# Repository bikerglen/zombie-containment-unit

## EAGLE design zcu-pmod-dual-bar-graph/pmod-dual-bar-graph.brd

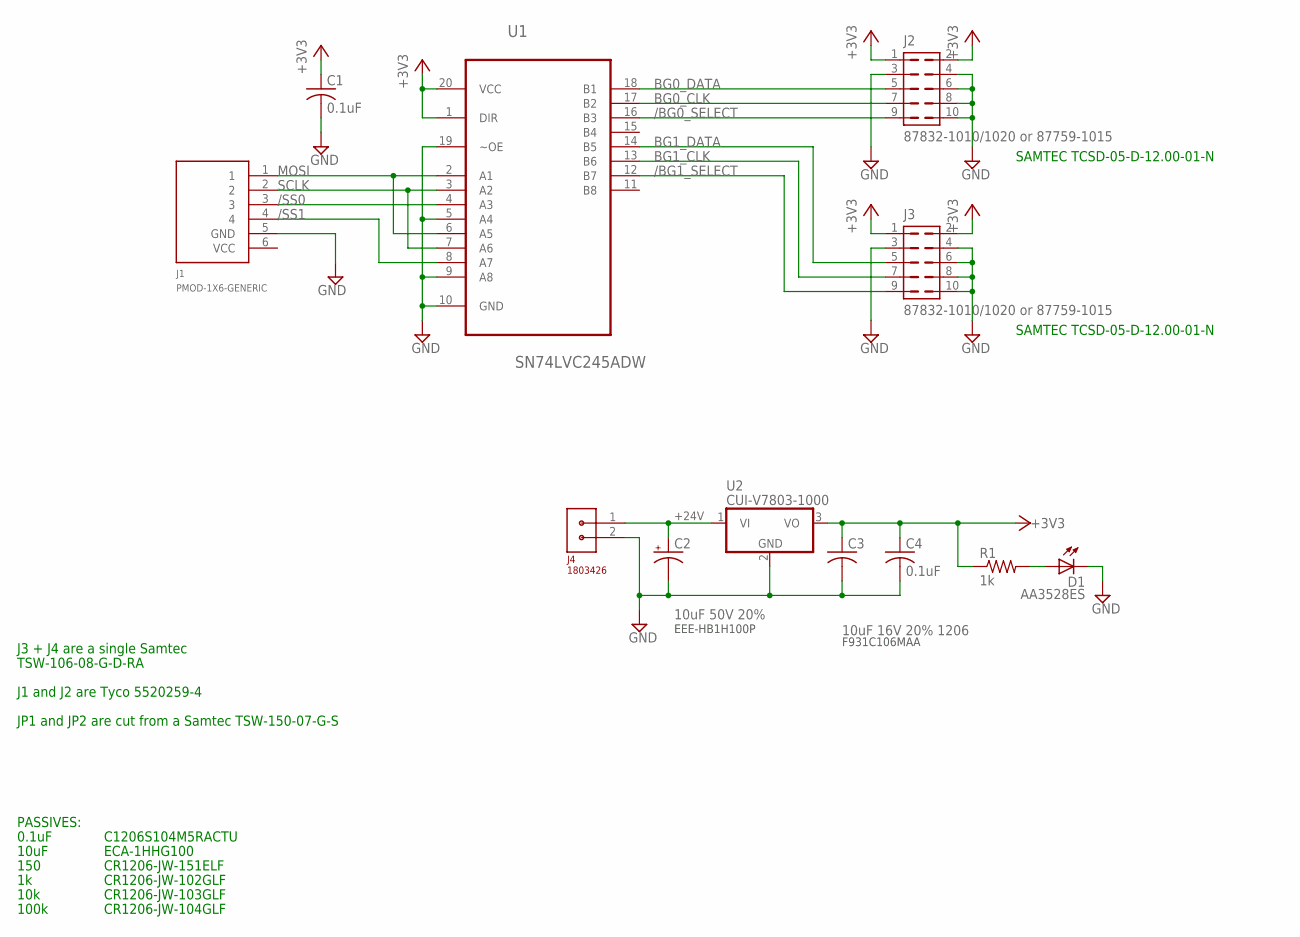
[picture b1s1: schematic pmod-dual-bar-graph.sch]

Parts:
C1, C4: 0.1uF; C1206
C2: 10uF 50V 20%; PANASONIC_D
C3: 10uF 16V 20% 1206; C1206
D1: AA3528ES; KA-3528ASYC
J1: PMOD-1X6-GENERIC; CON-PMOD-1X6
J2, J3: 87832-1010/1020 or 87759-1015; 87832-10
J4: 1803426; CON-PHOENIX-1803426-3.81-1X2
R1: 1k; R1206
U1: SN74LVC245ADW; SOIC127P1030X265-20N
U2: CUI-V7803-1000; CUI-78XX-1000

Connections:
+3V3: C1.1, C3.1, C4.1, J2.1, J2.2, J3.1, J3.2, R1.1, U1.1 (DIR), U1.20 (VCC), U2.3 (VO)
+24V: C2.+, J4.1, U2.1 (VI)
/BG0_SELECT: J2.9, U1.16 (B3)
/BG1_SELECT: J3.9, U1.12 (B7)
/SS0: J1.3, U1.4 (A3)
/SS1: J1.4, U1.8 (A7)
BG0_CLK: J2.7, U1.17 (B2)
BG0_DATA: J2.5, U1.18 (B1)
BG1_CLK: J3.7, U1.13 (B6)
BG1_DATA: J3.5, U1.14 (B5)
GND: C1.2, C2.-, C3.2, C4.2, D1.C, J1.5 (GND), J2.3, J2.4, J2.6, J2.8, J2.10, J3.3, J3.4, J3.6, J3.8, J3.10, J4.2, U1.5 (A4), U1.9 (A8), U1.10 (GND), U1.19 (~OE), U2.2 (GND)
MOSI: J1.1, U1.2 (A1), U1.6 (A5)
unnamed: D1.A, R1.2
SCLK: J1.2, U1.3 (A2), U1.7 (A6)

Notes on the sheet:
J3 + J4 are a single Samtec
TSW-106-08-G-D-RA
J1 and J2 are Tyco 5520259-4
JP1 and JP2 are cut from a Samtec TSW-150-07-G-S
0.1uF
C1206S104M5RACTU
150
10k
100k
CR1206-JW-102GLF
CR1206-JW-151ELF
CR1206-JW-104GLF
CR1206-JW-103GLF
PASSIVES:
10uF
ECA-1HHG100
SAMTEC TCSD-05-D-12.00-01-N
F931C106MAA
EEE-HB1H100P

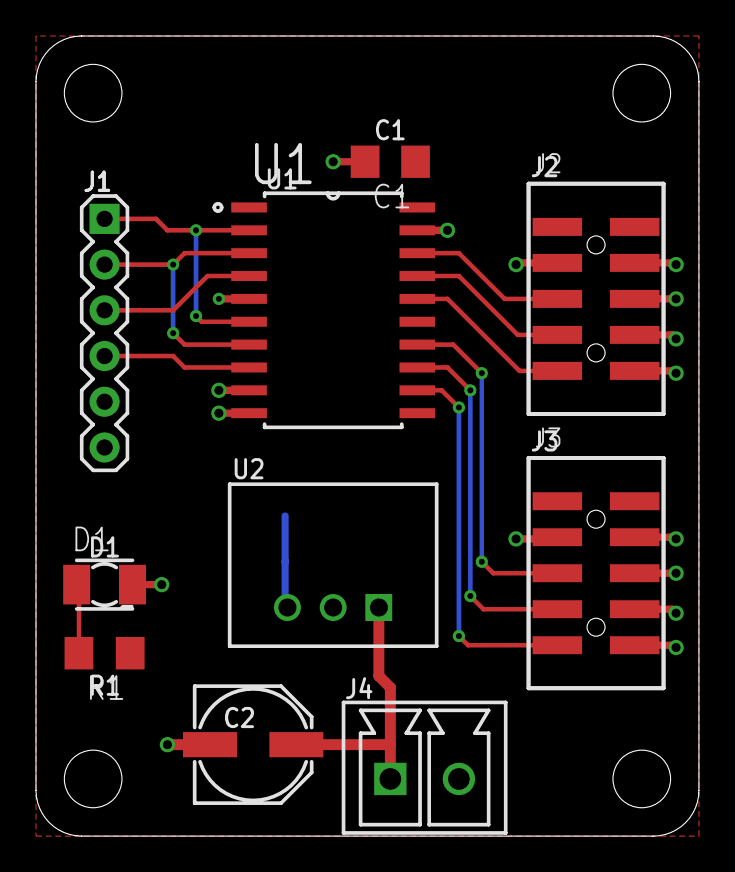
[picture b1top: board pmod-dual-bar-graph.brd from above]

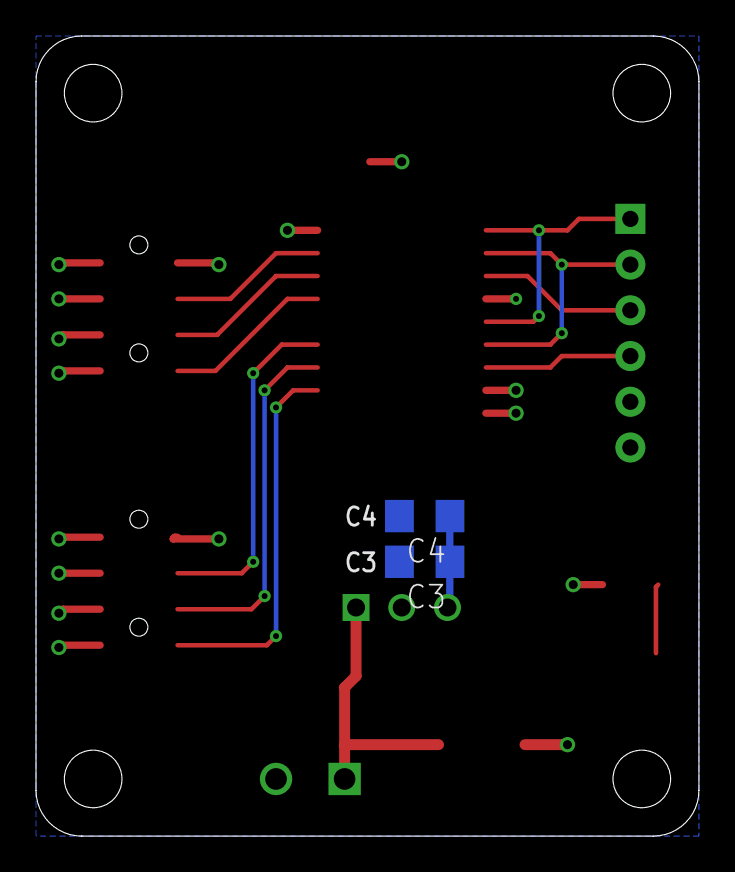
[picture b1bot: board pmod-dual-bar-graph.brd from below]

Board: 2 copper layers, 36.8 x 44.5 mm, 12 parts (2 on the bottom side), 14 nets.

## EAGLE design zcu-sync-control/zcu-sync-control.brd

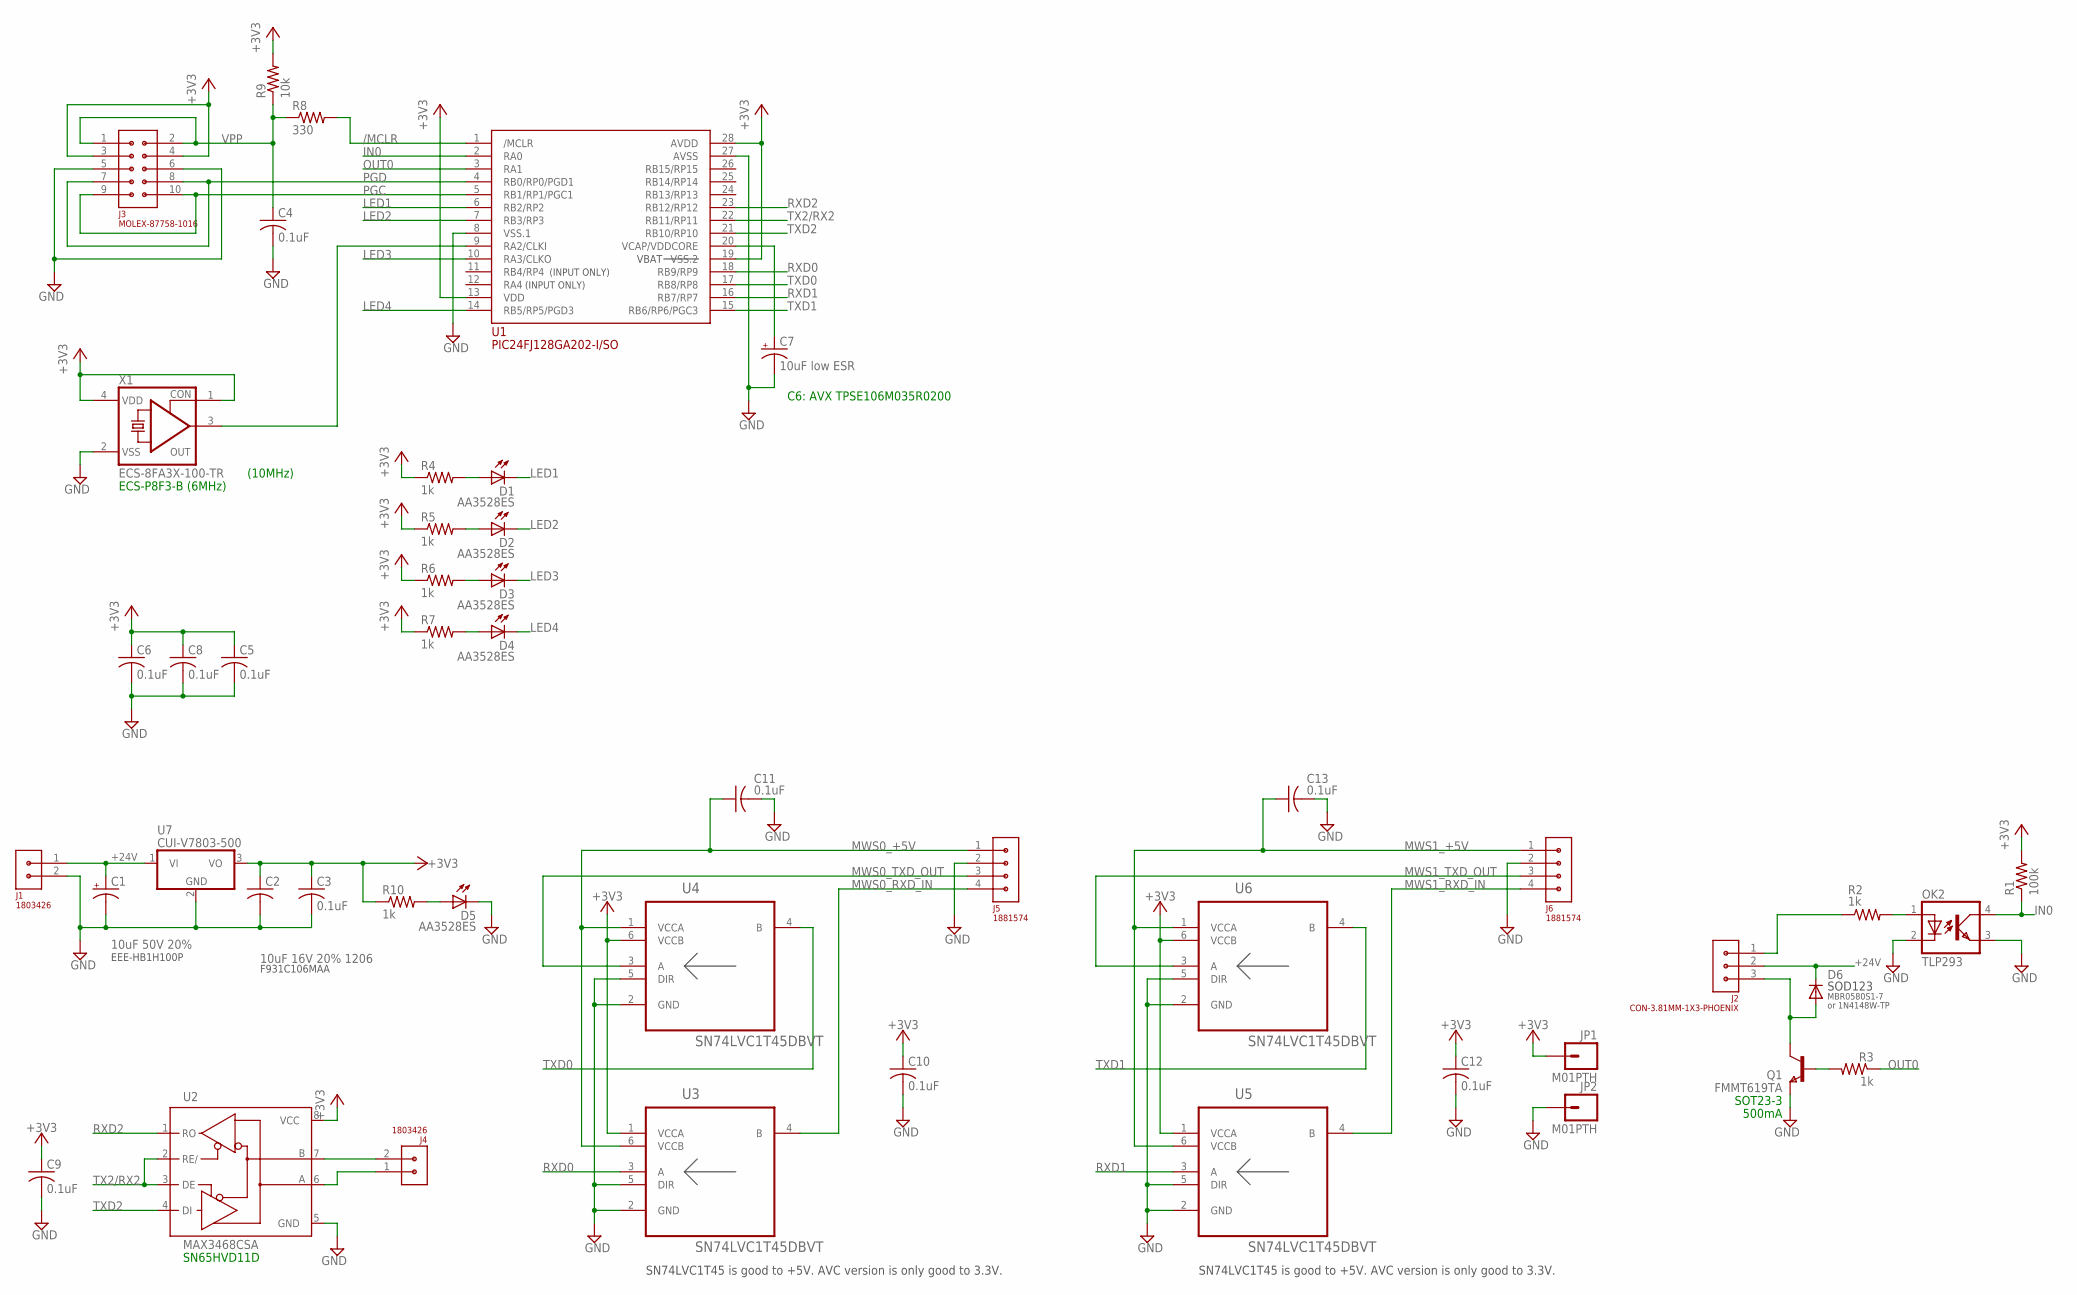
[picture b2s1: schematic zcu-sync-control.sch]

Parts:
C1: 10uF 50V 20%; PANASONIC_D
C2: 10uF 16V 20% 1206; C1206
C3, C4, C5, C6, C8, C9, C10, C11, C12, C13: 0.1uF; C1206
C7: 10uF low ESR; D/7343-31R
D1, D2, D3, D4, D5: AA3528ES; KA-3528ASYC
D6: 1N4148W-TP; SOD123
J1, J4: 1803426; CON-PHOENIX-1803426-3.81-1X2
J2: CON-3.81MM-1X3-PHOENIX; CON-PHOENIX-3.81-1X3
J3: MOLEX-87758-1016; CON-2MM-2X5
J5, J6: 1881574; CON-2.5MM-1X4-PHOENIX-1881574
JP1, JP2: M01PTH; 1X01
OK2: TLP293; MINI-FLAT-4
Q1: FMMT619TA; SOT-23
R1: 100k; R1206
R2, R3, R4, R5, R6, R7, R10: 1k; R1206
R8: 330; R1206
R9: 10k; R1206
U1: PIC24FJ128GA202-I/SO; SO28W
U2: MAX3468CSA; SO08
U3, U4, U5, U6: SN74LVC1T45DBVT; SOT95P280X145-6N
U7: CUI-V7803-500; CUI-78XX-500
X1: ECS-8FA3X-100-TR; 1100S

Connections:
+3V3: C2.1, C3.1, C5.1, C6.1, C8.1, C9.1, C10.1, C12.1, J3.3, J3.4, JP1.1, R1.2, R4.1, R5.1, R6.1, R7.1, R9.2, R10.1, U1.13 (VDD), U1.19 (VSS.2), U1.28 (AVDD), U2.8 (VCC), U3.1 (VCCA), U4.6 (VCCB), U5.1 (VCCA), U6.6 (VCCB), U7.3 (VO), X1.1 (CON), X1.4 (VDD)
+24V: C1.+, D6.C, J1.1, J2.2, U7.1 (VI)
/MCLR: R8.2, U1.1 (/MCLR)
D+: J4.1, U2.6 (A)
D-: J4.2, U2.7 (B)
GND: C1.-, C2.2, C3.2, C4.2, C5.2, C6.2, C7.-, C8.2, C9.2, C10.2, C11.2, C12.2, C13.2, D5.C, J1.2, J3.5, J3.6, J5.2, J6.2, JP2.1, OK2.2 (C), OK2.3 (EMIT), Q1.2 (E), U1.8 (VSS.1), U1.27 (AVSS), U2.5 (GND), U3.2 (GND), U3.5 (DIR), U4.2 (GND), U4.5 (DIR), U5.2 (GND), U5.5 (DIR), U6.2 (GND), U6.5 (DIR), U7.2 (GND), X1.2 (VSS)
IN0: OK2.4 (COL), R1.1, U1.2 (RA0)
LED1: D1.C, U1.6 (RB2/RP2)
LED2: D2.C, U1.7 (RB3/RP3)
LED3: D3.C, U1.10 (RA3/CLKO)
LED4: D4.C, U1.14 (RB5/RP5/PGD3)
MWS0_+5V: C11.1, J5.1, U3.6 (VCCB), U4.1 (VCCA)
MWS0_RXD_IN: J5.4, U3.4 (B)
MWS0_TXD_OUT: J5.3, U4.3 (A)
MWS1_+5V: C13.1, J6.1, U5.6 (VCCB), U6.1 (VCCA)
MWS1_RXD_IN: J6.4, U5.4 (B)
MWS1_TXD_OUT: J6.3, U6.3 (A)
unnamed: U1.9 (RA2/CLKI), X1.3 (OUT)
unnamed: D1.A, R4.2
unnamed: C7.+, U1.20 (VCAP/VDDCORE)
unnamed: D2.A, R5.2
unnamed: D3.A, R6.2
unnamed: OK2.1 (A), R2.2
unnamed: D4.A, R7.2
unnamed: J2.1, R2.1
unnamed: D6.A, J2.3, Q1.1 (C)
unnamed: Q1.3 (B), R3.2
unnamed: D5.A, R10.2
OUT0: R3.1, U1.3 (RA1)
PGC: J3.9, J3.10, U1.5 (RB1/RP1/PGC1)
PGD: J3.7, J3.8, U1.4 (RB0/RP0/PGD1)
RXD0: U1.18 (RB9/RP9), U3.3 (A)
RXD1: U1.16 (RB7/RP7), U5.3 (A)
RXD2: U1.23 (RB12/RP12), U2.1 (RO)
TX2/RX2: U1.22 (RB11/RP11), U2.2 (RE/), U2.3 (DE)
TXD0: U1.17 (RB8/RP8), U4.4 (B)
TXD1: U1.15 (RB6/RP6/PGC3), U6.4 (B)
TXD2: U1.21 (RB10/RP10), U2.4 (DI)
VPP: C4.1, J3.1, J3.2, R8.1, R9.1

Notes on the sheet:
SN74LVC1T45 is good to +5V. AVC version is only good to 3.3V.
SN65HVD11D
(10MHz)
ECS-P8F3-B (6MHz)
C6: AVX TPSE106M035R0200
SOT23-3
500mA
VBAT
SOD123
MBR0580S1-7
F931C106MAA
EEE-HB1H100P
(INPUT ONLY)
or 1N4148W-TP

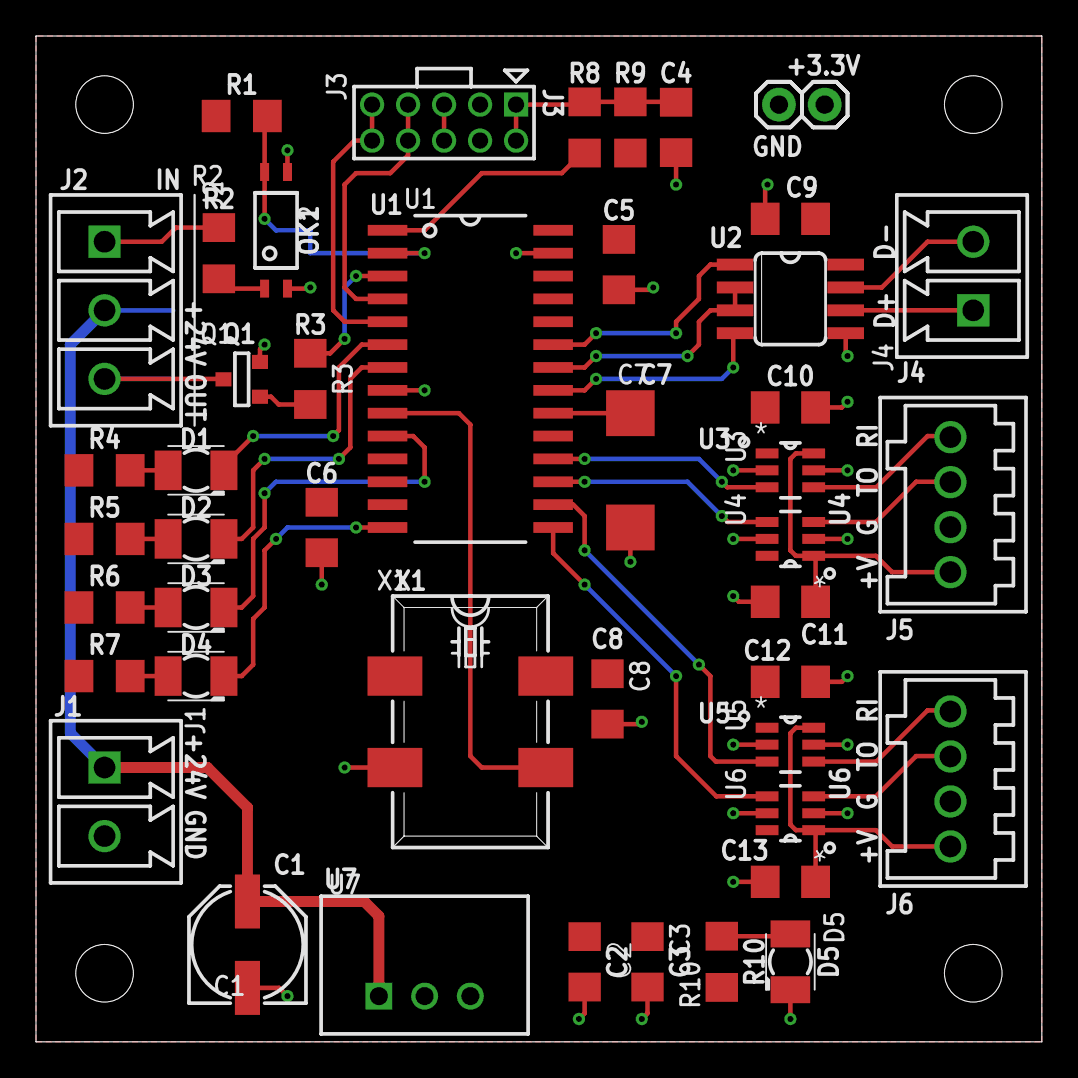
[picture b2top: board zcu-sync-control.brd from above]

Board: 2 copper layers, 55.9 x 55.9 mm, 47 parts (1 on the bottom side), 39 nets.

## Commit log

2017-02-19 initial checkin
2017-02-26 moved media / sync controller to its own subdirectory
2017-02-27 moved file
2017-09-09 updated to sw to correspond to new version of block diagram design where red alert lights are controlled by transistors and amber side lights are controlled by relays
2017-09-10 added dmx control of ambient lighting; 3 CK Colorbast 12 fixtures and 4 Eliminator Mini PAR UV fixtures
2017-09-21 added dmx controlled fogger channel
2017-10-23 added green side lights that turn on when smoke machine fires
2017-10-23 added gpl v3 license message
2017-10-23 initial checkin of dmx / pixel driver rtl
2017-10-23 initial checkin of Goertzel DTMF decoder and i2s interface
2017-10-23 added .xci IP files and packaged zip file
2017-10-23 added .xci files for IPs and packaged IP
2017-10-23 removed ILA block on dtmf decoder audio and tones
2017-12-22 add zybo constraints file
2022-10-03 add bar graph power / data buffer board
2022-10-03 rename directory
